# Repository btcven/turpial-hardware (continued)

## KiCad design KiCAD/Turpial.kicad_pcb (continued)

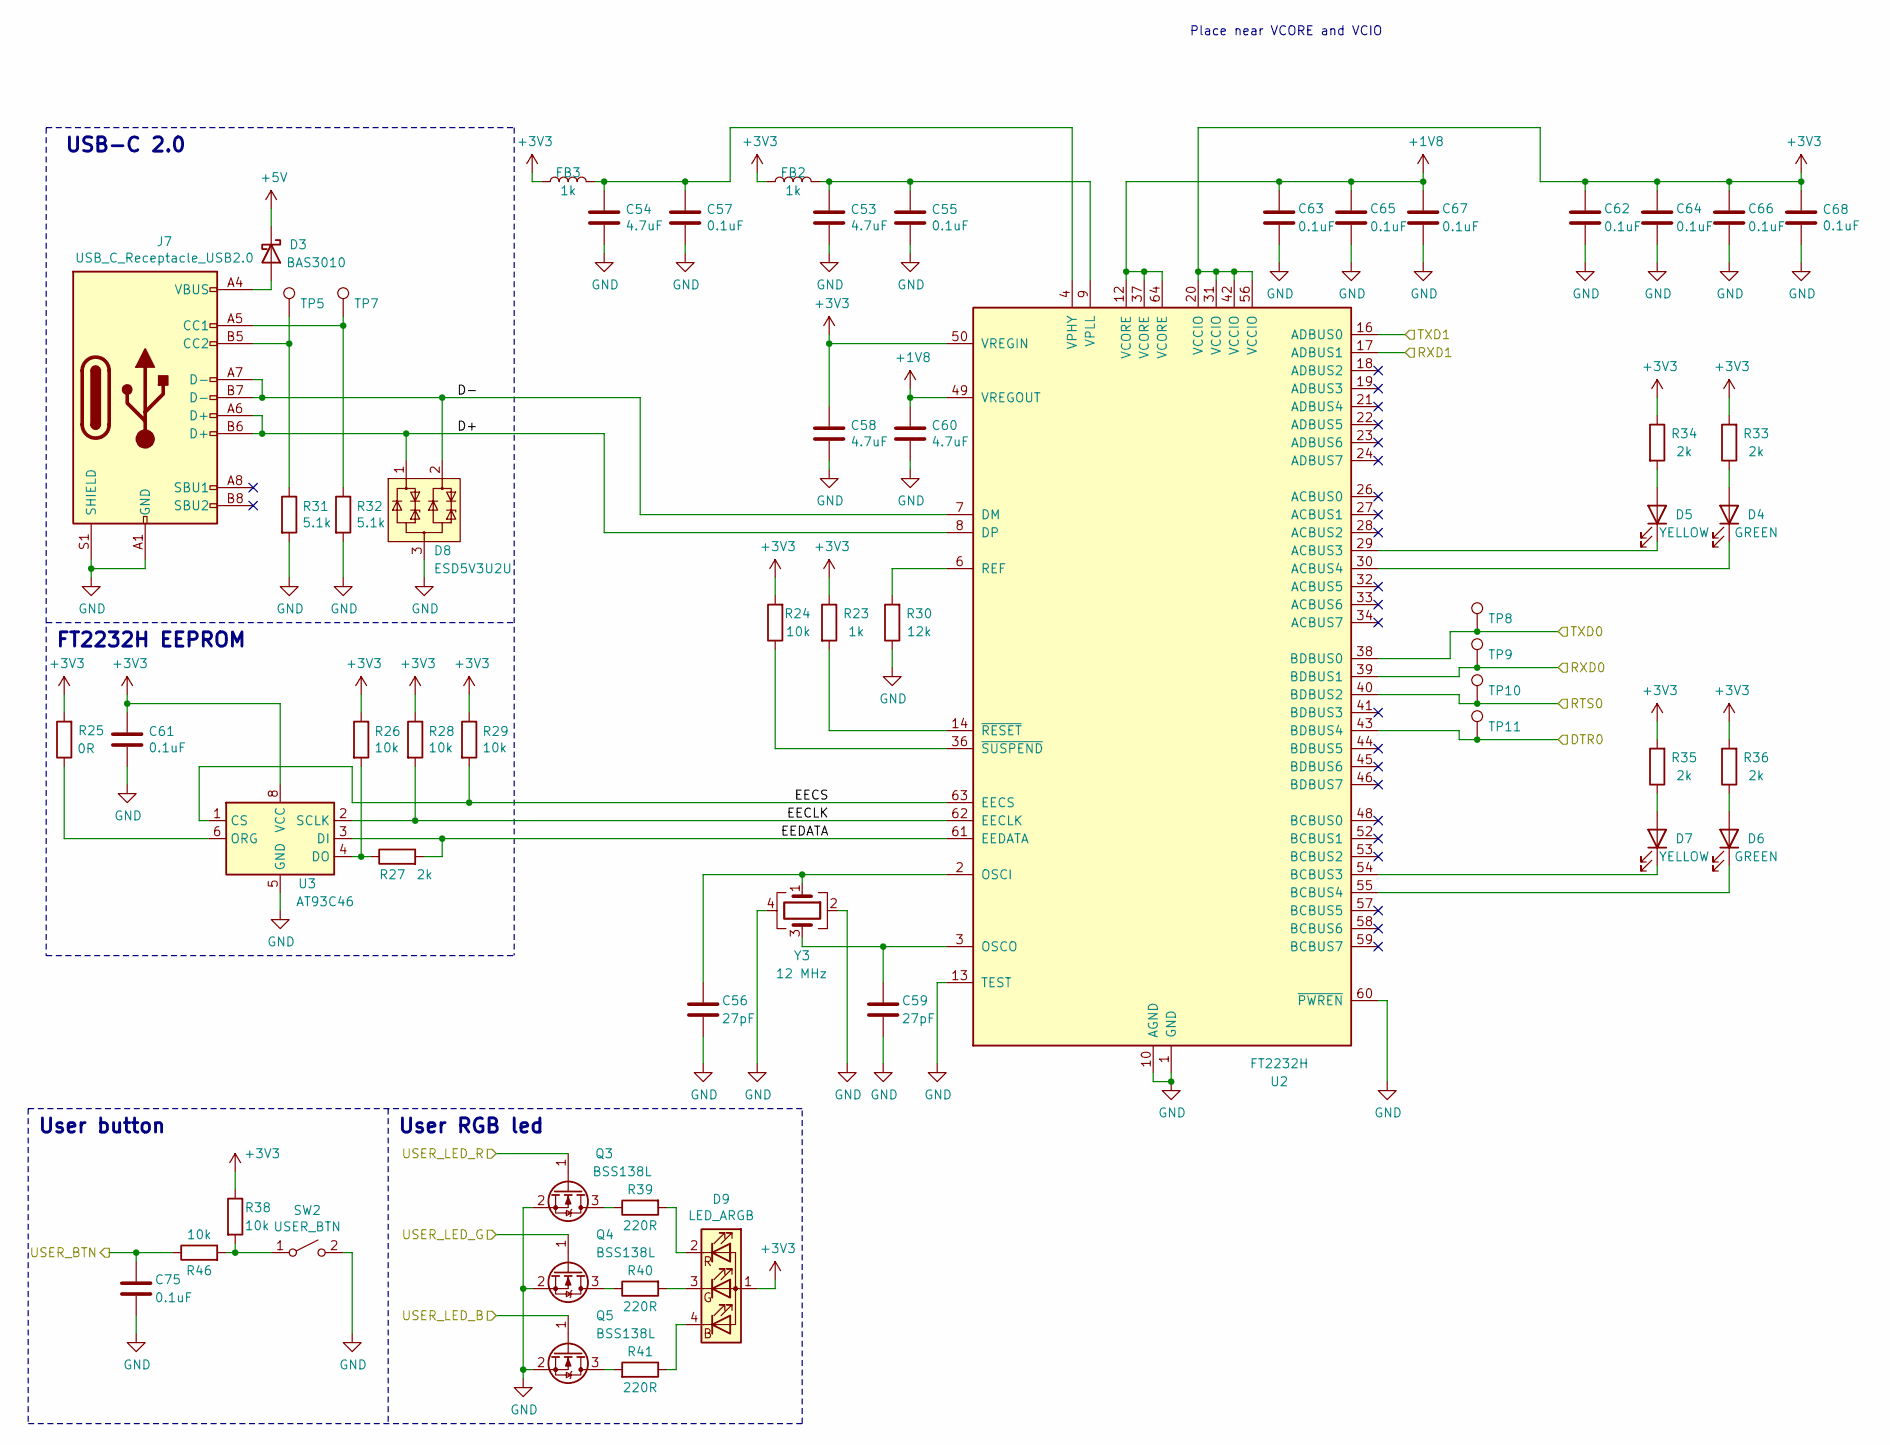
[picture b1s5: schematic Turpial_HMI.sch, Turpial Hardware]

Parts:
C53, C54, C58, C60: 4.7uF; C_0402_1005Metric; Manufacturer_Part_Number GRM155R61A475MEAAD; Mouser Part Number 81-GRM155R61A475MEAD
C55, C57, C61, C62, C63, C64, C65, C66, C67, C68, C75: 0.1uF; C_0402_1005Metric; Manufacturer_Part_Number GRM155R61H104KE19D; Mouser Part Number 81-GRM155R61H104KE9D
C56, C59: 27pF; C_0402_1005Metric; Manufacturer_Part_Number GJM1555C1H270JB01D; Mouser Part Number 81-GJM1555C1H270JB1D
D3: BAS3010; D_SOD-323; Manufacturer_Part_Number BAS3010A03WE6327HTSA1; Mouser Part Number 726-BAS3010A-03WE6
D4, D6: GREEN; LED_0603_1608Metric; Manufacturer_Part_Number LTST-C191KSKT; Mouser Part Number 859-LTST-C191KSKT
D5, D7: YELLOW; LED_0603_1608Metric; Manufacturer_Part_Number LTST-C191KGKT; Mouser Part Number 859-LTST-C191KGKT
D8: ESD5V3U2U; SOT-723; Manufacturer_Part_Number ESD5V3U2U03FH6327XTSA1; Mouser Part Number 726-5V3U2U03FH6327XT
D9: LED_ARGB; LED_HSMFC118; Manufacturer_Part_Number HSMF-C118; Mouser Part Number 630-HSMF-C118
FB2, FB3: 1k; L_0603_1608Metric; Manufacturer_Part_Number BLM18KG102SN1D; Mouser Part Number 81-BLM18KG102SN1D
J7: USB_C_Receptacle_USB2.0; CONN-USBC_SS-52400-003
Q3, Q4, Q5: BSS138L; SOT-23; Manufacturer_Part_Number BSS138L; Mouser Part Number 512-BSS138L
R23: 1k; R_0603_1608Metric; Manufacturer_Part_Number RC0603FR-071KL; Mouser Part Number 603-RC0603FR-071KL
R24, R26, R28, R29, R38, R46: 10k; R_0402_1005Metric; Manufacturer_Part_Number RC0402FR-0710KL; Mouser Part Number 603-RC0402FR-0710KL
R25: 0R; R_0402_1005Metric; Manufacturer_Part_Number RC0402JR-070RL; Mouser Part Number 603-RC0402JR-070RL
R27, R33, R34, R35, R36: 2k; R_0402_1005Metric; Manufacturer_Part_Number RC0402FR-072KL; Mouser Part Number 603-RC0402FR-072KL
R30: 12k; R_0402_1005Metric; Manufacturer_Part_Number RC0402FR-0712KL; Mouser Part Number 603-RC0402FR-0712KL
R31, R32: 5.1k; R_0402_1005Metric; Manufacturer_Part_Number RC0402FR-075K1L; Mouser Part Number 603-RC0402FR-075K1L
R39, R40, R41: 220R; R_0603_1608Metric; Manufacturer_Part_Number CRCW0603220RJNEAC; Mouser Part Number 71-CRCW0603220RJNEAC
SW2: USER_BTN; WS-TASU-Series
TP5: CC2; TestPoint_Pad_D1.0mm
TP7: CC1; TestPoint_Pad_D1.0mm
TP8: RXD0; TestPoint_Pad_D1.0mm
TP9: TXD0; TestPoint_Pad_D1.0mm
TP10: RTS0; TestPoint_Pad_D1.0mm
TP11: DTR0; TestPoint_Pad_D1.0mm
U2: FT2232H; LQFP-64_10x10mm_P0.5mm; Manufacturer_Part_Number FT2232HL-TRAY; Mouser Part Number 895-FT2232HL-TRAY
U3: AT93C46; SOIC-8_3.9x4.9mm_P1.27mm; Manufacturer_Part_Number AT93C46DN-SH-T; Mouser Part Number 556-A93C46DNSHT
Y3: 12 MHz; Crystal_SMD_3225-4Pin_3.2x2.5mm; Manufacturer_Part_Number ECS-120-12-33-AEN-TR; Mouser Part Number 520-120-12-33-AENT

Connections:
+1V8: C60.1, C63.1, C65.1, C67.1, U2.12 (VCORE), U2.37 (VCORE), U2.49 (VREGOUT), U2.64 (VCORE)
+3V3: C58.1, C61.1, C62.1, C64.1, C66.1, C68.1, D9.1 (A), FB2.1, FB3.1, R23.1, R24.2, R25.2, R26.1, R28.1, R29.1, R33.2, R34.1, R35.2, R36.2, R38.1, U2.20 (VCCIO), U2.31 (VCCIO), U2.42 (VCCIO), U2.50 (VREGIN), U2.56 (VCCIO), U3.8 (VCC); also elsewhere on the board
+5V: D3.1 (K); also elsewhere on the board
/Turpial_HMI/D+: D8.1, J7.A6 (D+), J7.B6 (D+), U2.8 (DP)
/Turpial_HMI/D-: D8.2, J7.A7 (D-), J7.B7 (D-), U2.7 (DM)
/Turpial_HMI/EECLK: R28.2, U2.62 (EECLK), U3.2 (SCLK)
/Turpial_HMI/EECS: R29.2, U2.63 (EECS), U3.1 (CS)
/Turpial_HMI/EEDATA: R27.2, U2.61 (EEDATA), U3.3 (DI)
CC1312_LED_B: Q5.1 (G); also elsewhere on the board
CC1312_LED_G: Q4.1 (G); also elsewhere on the board
CC1312_LED_R: Q3.1 (G); also elsewhere on the board
CC1312_UART0_RXD: U2.16 (ADBUS0); also elsewhere on the board
CC1312_UART0_TXD: U2.17 (ADBUS1); also elsewhere on the board
CC1312_USER_BTN: C75.1, R46.1; also elsewhere on the board
ESP32_DTR: TP11.1, U2.43 (BDBUS4); also elsewhere on the board
ESP32_RTS: TP10.1, U2.40 (BDBUS2); also elsewhere on the board
ESP32_UART0_RXD: TP8.1, U2.38 (BDBUS0); also elsewhere on the board
ESP32_UART0_TXD: TP9.1, U2.39 (BDBUS1); also elsewhere on the board
GND: C53.2, C54.2, C55.2, C56.2, C57.2, C58.2, C59.2, C60.2, C61.2, C62.2, C63.2, C64.2, C65.2, C66.2, C67.2, C68.2, C75.2, D8.3, J7.A1 (GND), J7.A12 (GND), J7.B1 (GND), J7.B12 (GND), J7.S1 (SHIELD), Q3.2 (S), Q4.2 (S), Q5.2 (S), R30.1, R31.2, R32.2, SW2.2 (B), U2.1 (GND), U2.5 (GND), U2.10 (AGND), U2.11 (GND), U2.13 (TEST), U2.15 (GND), U2.25 (GND), U2.35 (GND), U2.47 (GND), U2.51 (GND), U2.60 (~PWREN), U3.5 (GND), Y3.2, Y3.4; also elsewhere on the board
unnamed: C53.1, C55.1, FB2.2, U2.9 (VPLL)
unnamed: C54.1, C57.1, FB3.2, U2.4 (VPHY)
unnamed: C56.1, U2.2 (OSCI), Y3.1
unnamed: C59.1, U2.3 (OSCO), Y3.3
unnamed: D3.2 (A), J7.A4 (VBUS), J7.A9 (VBUS), J7.B4 (VBUS), J7.B9 (VBUS)
unnamed: D4.1 (K), U2.30 (ACBUS4)
unnamed: D4.2 (A), R33.1
unnamed: D5.1 (K), U2.29 (ACBUS3)
unnamed: D5.2 (A), R34.2
unnamed: D6.1 (K), U2.55 (BCBUS4)
unnamed: D6.2 (A), R36.1
unnamed: D7.1 (K), U2.54 (BCBUS3)
unnamed: D7.2 (A), R35.1
unnamed: D9.2 (RK), R39.2
unnamed: D9.3 (GK), R40.2
unnamed: D9.4 (BK), R41.1
unnamed: J7.A5 (CC1), R32.1, TP7.1
unnamed: J7.B5 (CC2), R31.1, TP5.1
unnamed: Q3.3 (D), R39.1
unnamed: Q4.3 (D), R40.1
unnamed: Q5.3 (D), R41.2
unnamed: R23.2, U2.14 (~RESET)
unnamed: R24.1, U2.36 (~SUSPEND)
unnamed: R25.1, U3.6 (ORG)
unnamed: R26.2, R27.1, U3.4 (DO)
unnamed: R30.2, U2.6 (REF)
unnamed: R38.2, R46.2, SW2.1 (A)

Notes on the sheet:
User button
FT2232H EEPROM
User RGB led
Place near VCORE and VCIO
USB-C 2.0

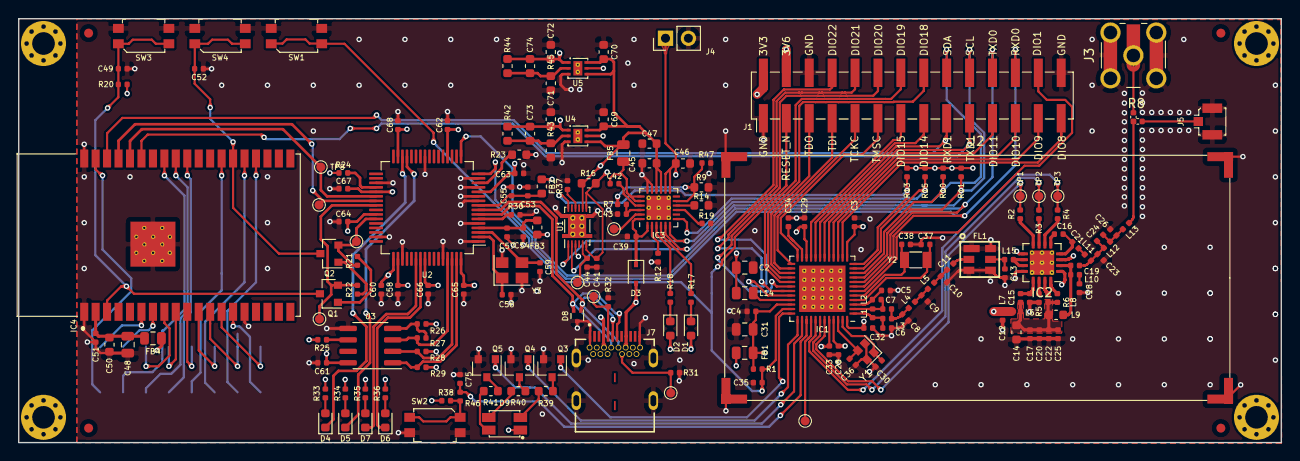
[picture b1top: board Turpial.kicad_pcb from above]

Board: 4 copper layers, 140.0 x 47.0 mm, 197 parts (1 on the bottom side), 148 nets.

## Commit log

2021-02-18 Turpial Hardware v0.3.3
